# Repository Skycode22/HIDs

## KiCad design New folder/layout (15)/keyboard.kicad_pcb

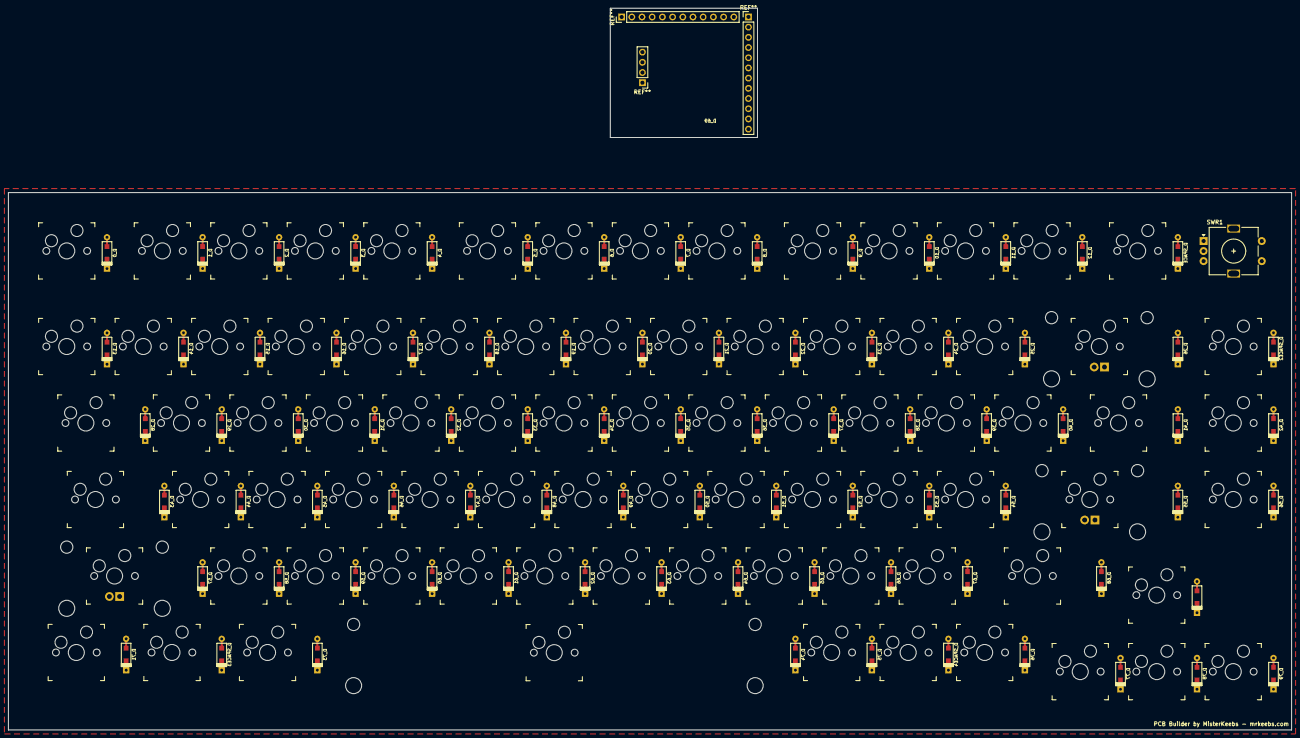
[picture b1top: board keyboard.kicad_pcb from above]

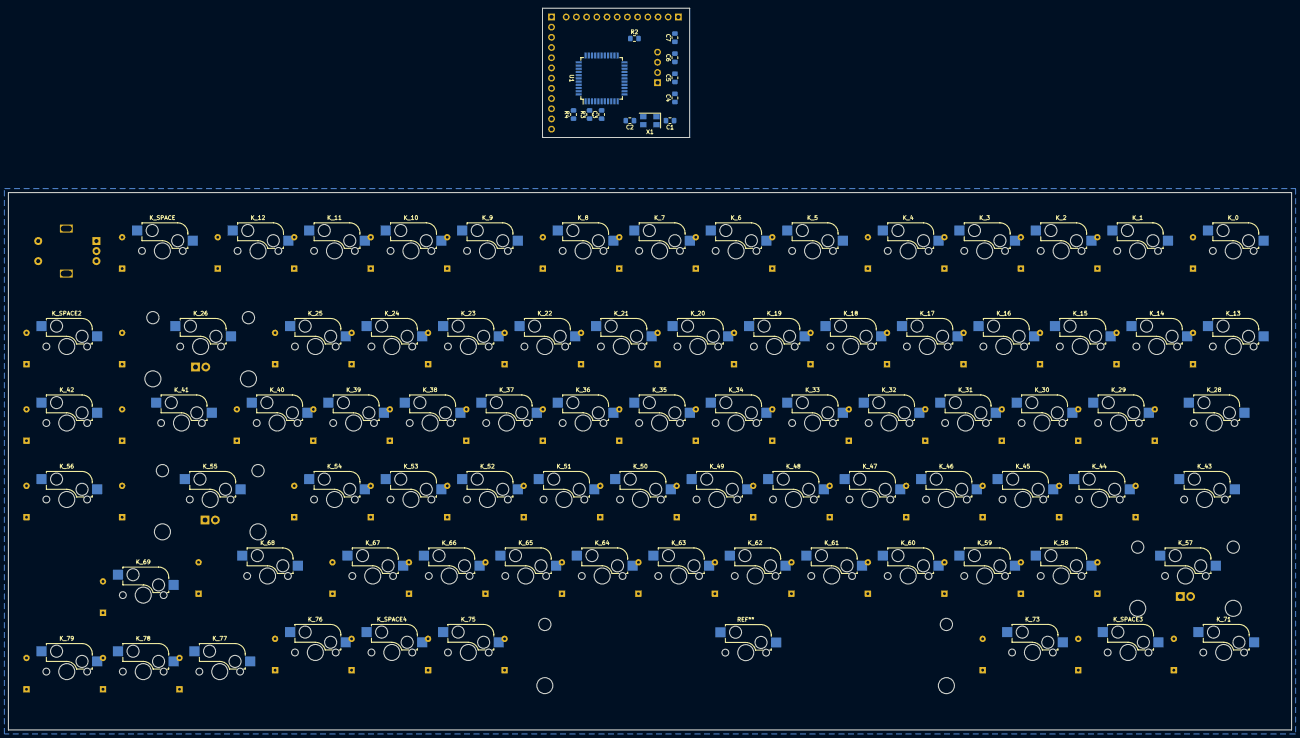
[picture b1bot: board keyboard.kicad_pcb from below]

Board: 2 copper layers, 319.6 x 133.8 mm, 175 parts (12 on the bottom side), 111 nets, no tracks yet.

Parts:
C1, C2, C3, C4, C5, C6, C7: 22pF; C_0805_2012Metric_Pad1.15x1.40mm_HandSolder
D_0, D_1, D_2, D_3, D_4, D_5, D_6, D_7, D_8, D_9, D_10, D_11, D_12, D_13, D_14, D_15, D_16, D_17, D_18, D_19, D_20, D_21, D_22, D_23, D_24, D_25, D_26, D_28, D_29, D_30, D_31, D_32, D_33, D_34, D_35, D_36, D_37, D_38, D_39, D_40, D_41, D_42, D_43, D_44, D_45, D_46, D_47, D_48, D_49, D_50, D_51, D_52, D_53, D_54, D_55, D_56, D_57, D_58, D_59, D_60, D_61, D_62, D_63, D_64, D_65, D_66, D_67, D_68, D_69, D_71, D_73, D_74, D_75, D_76, D_77, D_78, D_79: D; D_SOD123_axial
D_SPACE, D_SPACE2, D_SPACE3, D_SPACE4: D; D_SOD123_axial
K_0, K_1, K_2, K_3, K_4, K_5, K_6, K_7, K_8, K_9, K_10, K_11, K_12, K_13, K_14, K_15, K_16, K_17, K_18, K_19, K_20, K_21, K_22, K_23, K_24, K_25, K_28, K_29, K_30, K_31, K_32, K_33, K_34, K_35, K_36, K_37, K_38, K_39, K_40, K_41, K_42, K_43, K_44, K_45, K_46, K_47, K_48, K_49, K_50, K_51, K_52, K_53, K_54, K_56, K_58, K_59, K_60, K_61, K_62, K_63, K_64, K_65, K_66, K_67, K_68, K_69, K_71, K_73, K_75, K_76, K_77, K_78, K_79: KEYSW; Kailh_socket_MX
K_26, K_55, K_57: KEYSW; Kailh_socket_MX_led stab
K_74: KEYSW; STAB_MX_6.25u
K_SPACE, K_SPACE2, K_SPACE3, K_SPACE4: KEYSW; Kailh_socket_MX
R2: 10k; R_0805_2012Metric_Pad1.15x1.40mm_HandSolder
R3, R4: 22; R_0805_2012Metric_Pad1.15x1.40mm_HandSolder
SWR1: Rotary_Encoder_Switch; RotaryEncoder_Alps_EC11E-Switch_Vertical_H20mm
U1: ATMEGA32U4; TQFP-44_10x10mm_P0.8mm
X1: XTAL_GND; Crystal_SMD_5032-4Pin_5.0x3.2mm

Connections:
/col0: K_0.1, K_13.1, K_28.1, K_43.1, K_71.1, U1.12
/col1: K_1.1, K_14.1, K_57.1, K_SPACE3.1, U1.31
/col2: K_2.1, K_15.1, K_29.1, K_44.1, K_58.1, U1.32
/col3: K_3.1, K_16.1, K_30.1, K_45.1, K_59.1, K_73.1, U1.18
/col4: K_4.1, K_17.1, K_31.1, K_46.1, K_60.1, U1.19
/col5: K_18.1, K_32.1, K_47.1, K_61.1, U1.20
/col6: K_5.1, K_19.1, K_33.1, K_48.1, K_62.1, U1.21
/col7: K_6.1, K_20.1, K_34.1, K_49.1, K_63.1, U1.25
/col8: K_7.1, K_21.1, K_35.1, K_50.1, K_64.1, U1.22
/col9: K_8.1, K_22.1, K_36.1, K_51.1, K_65.1, U1.26
/col10: K_9.1, K_23.1, K_37.1, K_52.1, K_66.1, K_75.1, U1.27
/col11: K_10.1, K_24.1, K_38.1, K_53.1, K_67.1, K_SPACE4.1, U1.41
/col12: K_11.1, K_25.1, K_39.1, K_54.1, K_76.1, U1.40
/col13: K_12.1, K_40.1, K_55.1, K_68.1, K_77.1, U1.39
/col14: K_26.1, K_41.1, K_69.1, K_78.1, K_SPACE.1, U1.38
/col15: K_42.1, K_56.1, K_79.1, K_SPACE2.1, U1.37
/row0: D_0.1, D_1.1, D_2.1, D_3.1, D_4.1, D_5.1, D_6.1, D_7.1, D_8.1, D_9.1, D_10.1, D_11.1, D_12.1, D_SPACE.1, U1.8
/row1: D_13.1, D_14.1, D_15.1, D_16.1, D_17.1, D_18.1, D_19.1, D_20.1, D_21.1, D_22.1, D_23.1, D_24.1, D_25.1, D_26.1, D_SPACE2.1, U1.9
/row2: D_28.1, D_29.1, D_30.1, D_31.1, D_32.1, D_33.1, D_34.1, D_35.1, D_36.1, D_37.1, D_38.1, D_39.1, D_40.1, D_41.1, D_42.1, U1.10
/row3: D_43.1, D_44.1, D_45.1, D_46.1, D_47.1, D_48.1, D_49.1, D_50.1, D_51.1, D_52.1, D_53.1, D_54.1, D_55.1, D_56.1, U1.11
/row4: D_57.1, D_58.1, D_59.1, D_60.1, D_61.1, D_62.1, D_63.1, D_64.1, D_65.1, D_66.1, D_67.1, D_68.1, U1.28
/row5: D_69.1, D_71.1, D_73.1, D_74.1, D_75.1, D_76.1, D_SPACE3.1, D_SPACE4.1, U1.29
/row6: D_77.1, D_78.1, D_79.1, U1.30
GND: C1.2, C2.2, C3.2, C4.2, C5.2, C6.2, C7.2, R2.2, U1.5, U1.15, U1.23, X1.2, X1.4
unnamed: C1.1, U1.16, X1.1
unnamed: C2.1, U1.17, X1.3
unnamed: C3.1, U1.6
unnamed: D_0.2, K_0.2
unnamed: D_1.2, K_1.2
unnamed: D_2.2, K_2.2
unnamed: D_3.2, K_3.2
unnamed: D_4.2, K_4.2
unnamed: D_5.2, K_5.2
unnamed: D_6.2, K_6.2
unnamed: D_7.2, K_7.2
unnamed: D_8.2, K_8.2
unnamed: D_9.2, K_9.2
unnamed: D_10.2, K_10.2
unnamed: D_11.2, K_11.2
unnamed: D_12.2, K_12.2
unnamed: D_13.2, K_13.2
unnamed: D_14.2, K_14.2
unnamed: D_15.2, K_15.2
unnamed: D_16.2, K_16.2
unnamed: D_17.2, K_17.2
unnamed: D_18.2, K_18.2
unnamed: D_19.2, K_19.2
unnamed: D_20.2, K_20.2
unnamed: D_21.2, K_21.2
unnamed: D_22.2, K_22.2
unnamed: D_23.2, K_23.2
unnamed: D_24.2, K_24.2
unnamed: D_25.2, K_25.2
unnamed: D_26.2, K_26.2
unnamed: D_28.2, K_28.2
unnamed: D_29.2, K_29.2
unnamed: D_30.2, K_30.2
unnamed: D_31.2, K_31.2
unnamed: D_32.2, K_32.2
unnamed: D_33.2, K_33.2
unnamed: D_34.2, K_34.2
unnamed: D_35.2, K_35.2
unnamed: D_36.2, K_36.2
unnamed: D_37.2, K_37.2
unnamed: D_38.2, K_38.2
unnamed: D_39.2, K_39.2
unnamed: D_40.2, K_40.2
unnamed: D_41.2, K_41.2
unnamed: D_42.2, K_42.2
unnamed: D_43.2, K_43.2
unnamed: D_44.2, K_44.2
unnamed: D_45.2, K_45.2
unnamed: D_46.2, K_46.2
unnamed: D_47.2, K_47.2
unnamed: D_48.2, K_48.2
unnamed: D_49.2, K_49.2
unnamed: D_50.2, K_50.2
unnamed: D_51.2, K_51.2
unnamed: D_52.2, K_52.2
unnamed: D_53.2, K_53.2
unnamed: D_54.2, K_54.2
unnamed: D_55.2, K_55.2
unnamed: D_56.2, K_56.2
unnamed: D_57.2, K_57.2
unnamed: D_58.2, K_58.2
unnamed: D_59.2, K_59.2
unnamed: D_60.2, K_60.2
unnamed: D_61.2, K_61.2
unnamed: D_62.2, K_62.2
unnamed: D_63.2, K_63.2
unnamed: D_64.2, K_64.2
unnamed: D_65.2, K_65.2
unnamed: D_66.2, K_66.2
unnamed: D_67.2, K_67.2
unnamed: D_68.2, K_68.2
unnamed: D_69.2, K_69.2
unnamed: D_71.2, K_71.2
unnamed: D_73.2, K_73.2
unnamed: D_75.2, K_75.2
unnamed: D_76.2, K_76.2
unnamed: D_77.2, K_77.2
unnamed: D_78.2, K_78.2
unnamed: D_79.2, K_79.2
unnamed: D_SPACE2.2, K_SPACE2.2
unnamed: D_SPACE3.2, K_SPACE3.2
unnamed: D_SPACE4.2, K_SPACE4.2
unnamed: D_SPACE.2, K_SPACE.2
unnamed: R2.1, U1.33
unnamed: R3.1, U1.3
unnamed: R4.1, U1.4
VCC: C4.1, C5.1, C6.1, C7.1, U1.2, U1.14, U1.24

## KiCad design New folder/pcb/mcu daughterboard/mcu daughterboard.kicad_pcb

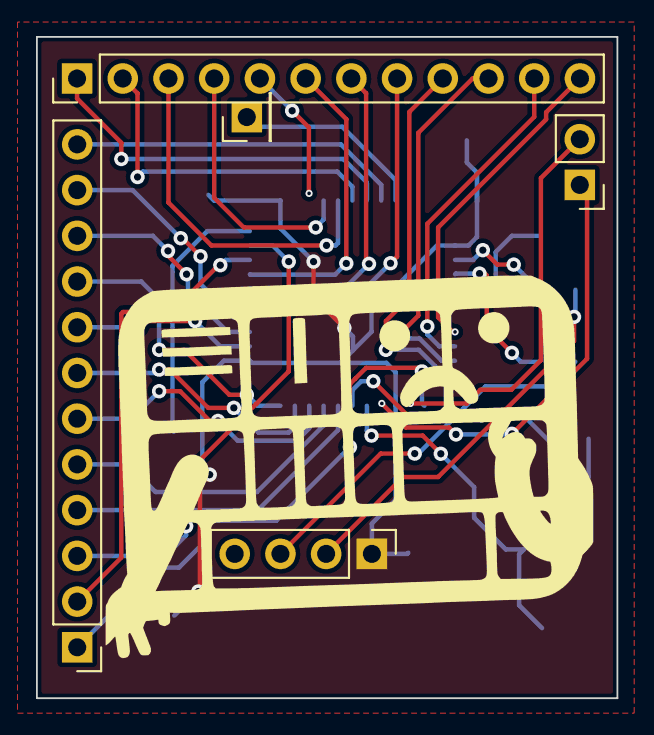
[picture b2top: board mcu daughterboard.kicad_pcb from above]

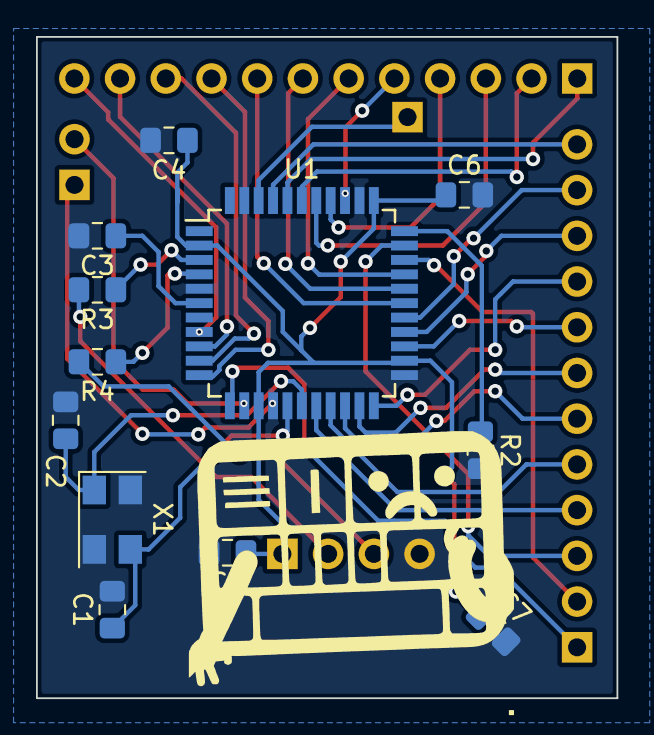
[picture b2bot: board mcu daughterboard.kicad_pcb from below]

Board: 2 copper layers, 32.2 x 36.7 mm, 17 parts (12 on the bottom side), 35 nets.

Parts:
*: '; PinHeader_1x04_P2.54mm_Vertical
*#2: '; PinHeader_1x01_P2.54mm_Vertical
*#3: PinHeader_1x02_P2.54mm_Vertical
*#4: 1; PinHeader_1x12_P2.54mm_Vertical
*#5: '; PinHeader_1x12_P2.54mm_Vertical
C1, C2, C3, C4, C5, C6, C7: 22pF; C_0805_2012Metric_Pad1.15x1.40mm_HandSolder
R2: 10k; R_0805_2012Metric_Pad1.15x1.40mm_HandSolder
R3, R4: 22; R_0805_2012Metric_Pad1.15x1.40mm_HandSolder
U1: ATMEGA32U4; TQFP-44_10x10mm_P0.8mm
X1: XTAL_GND; Crystal_SMD_5032-4Pin_5.0x3.2mm

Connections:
/col0: *#5.1, U1.12
/col1: *#5.2, U1.31
/col2: *#5.3, U1.32
/col3: *#5.4, U1.18
/col4: *#5.5, U1.19
/col5: *#5.6, U1.20
/col6: *#5.7, U1.21
/col7: *#5.8, U1.25
/col8: *#5.9, U1.22
/col9: *#5.10, U1.26
/col10: *#5.11, U1.27
/col11: *#5.12, U1.41
/col12: *#4.1, U1.40
/col13: *#4.2, U1.39
/col14: *#4.3, U1.38
/col15: *#4.4, U1.37
/row0: *#4.12, U1.8
/row1: *#4.11, U1.9
/row2: *#4.10, U1.10
/row3: *#4.9, U1.11
/row4: *#4.8, U1.28
/row5: *#4.7, U1.29
/row6: *#4.6, U1.30
GND: *.4, C1.2, C2.2, C3.2, C4.2, C5.2, C6.2, C7.2, R2.2, U1.5, U1.15, U1.23, U1.35, U1.43, X1.2, X1.4
unnamed: C1.1, U1.16, X1.1
unnamed: C2.1, U1.17, X1.3
unnamed: C3.1, U1.6
unnamed: R2.1, U1.33
unnamed: R3.1, U1.3
unnamed: R4.1, U1.4
unnamed: *#2.1, U1.42
unnamed: *#4.5, U1.36
unnamed: *.2, R3.2
unnamed: *.3, R4.2
VCC: *.1, C4.1, C5.1, C6.1, C7.1, U1.2, U1.14, U1.24, U1.34
